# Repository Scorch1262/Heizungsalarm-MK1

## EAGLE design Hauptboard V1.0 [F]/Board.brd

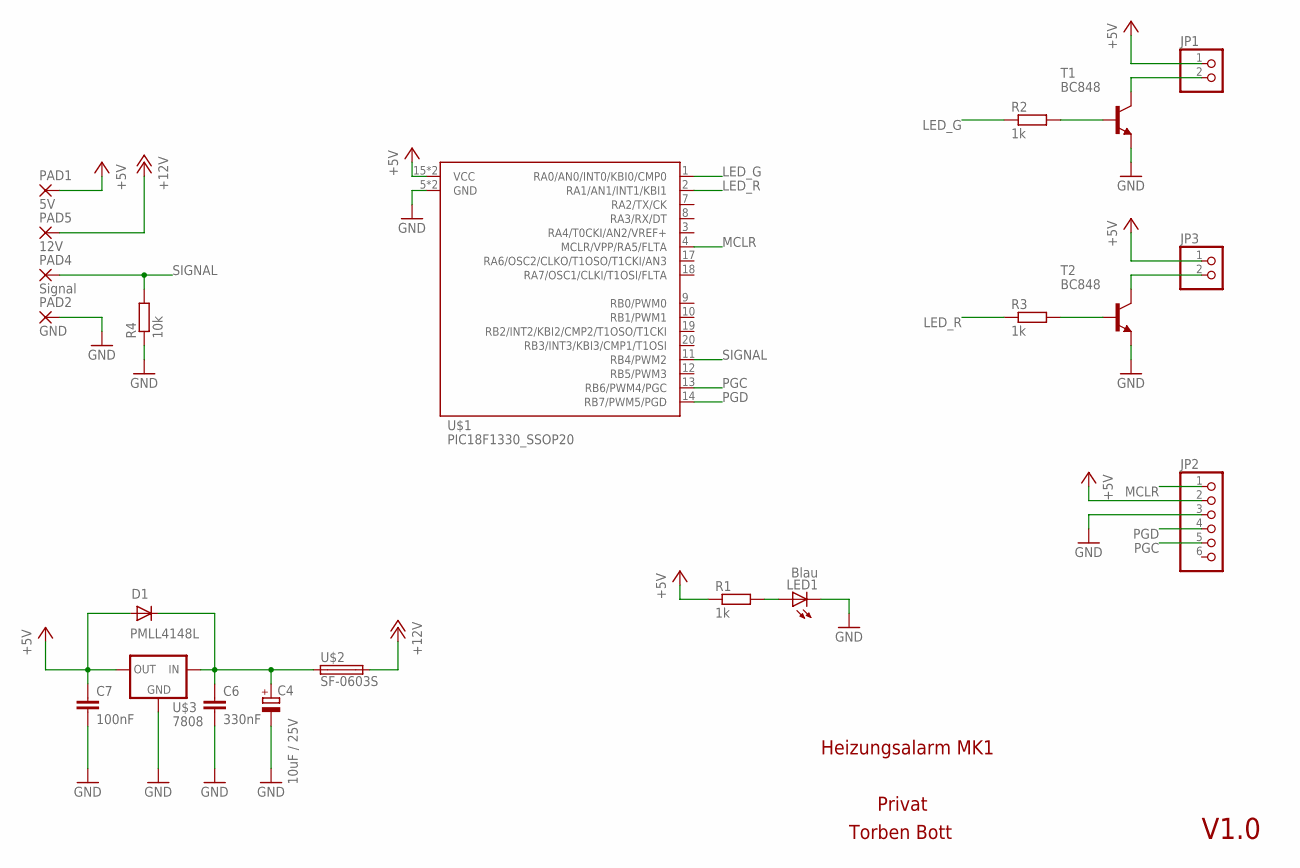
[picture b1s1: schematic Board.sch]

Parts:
C4: 10uF / 25V; D/7343-31R
C6: 330nF; C0805
C7: 100nF; C0805
D1: PMLL4148L; SOD80C
JP1, JP3: PINHD-1X2/90; 1X02/90
JP2: PINHD-1X6; 1X06
LED1: Blau; CHIP-LED0805
PAD1: 5V; 5-1,8
PAD2: GND; 5-1,8
PAD4: Signal; 5-1,8
PAD5: 12V; 5-1,8
R1, R2, R3: 1k; R0805
R4: 10k; R0805
T1, T2: BC848; SOT23
U$1: PIC18F1330_SSOP20; SSOP20
U$2: SF-0603S; R0603
U$3: 7808; SOT89

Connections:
+5V: C7.1, D1.2 (A), JP1.1, JP2.2, JP3.1, PAD1.1, R1.1, U$1.15 (VCC), U$1.16 (VCC), U$3.1 (IN)
+12V: PAD5.1, U$2.2
GND: C4.-, C6.2, C7.2, JP2.3, LED1.C, PAD2.1, R4.1, T1.2 (E), T2.2 (E), U$1.5 (GND), U$1.6 (GND), U$3.2 (GND), U$3.2@1 (GND)
LED_G: R2.1, U$1.1 (RA0/AN0/INT0/KBI0/CMP0)
LED_R: R3.1, U$1.2 (RA1/AN1/INT1/KBI1)
MCLR: JP2.1, U$1.4 (MCLR/VPP/RA5/FLTA)
unnamed: R2.2, T1.1 (B)
unnamed: LED1.A, R1.2
unnamed: C4.+, C6.1, D1.1 (K), U$2.1, U$3.3 (OUT)
unnamed: JP1.2, T1.3 (C)
unnamed: R3.2, T2.1 (B)
unnamed: JP3.2, T2.3 (C)
PGC: JP2.5, U$1.13 (RB6/PWM4/PGC)
PGD: JP2.4, U$1.14 (RB7/PWM5/PGD)
SIGNAL: PAD4.1, R4.2, U$1.11 (RB4/PWM2)

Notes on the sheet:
Heizungsalarm MK1
Privat
Torben Bott
V1.0

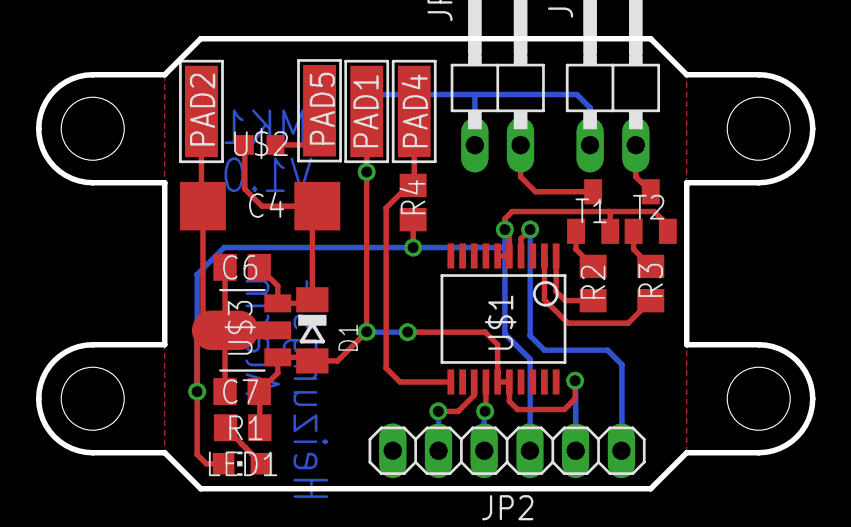
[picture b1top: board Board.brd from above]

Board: 2 copper layers, 43.0 x 25.0 mm, 21 parts (0 on the bottom side), 15 nets.
